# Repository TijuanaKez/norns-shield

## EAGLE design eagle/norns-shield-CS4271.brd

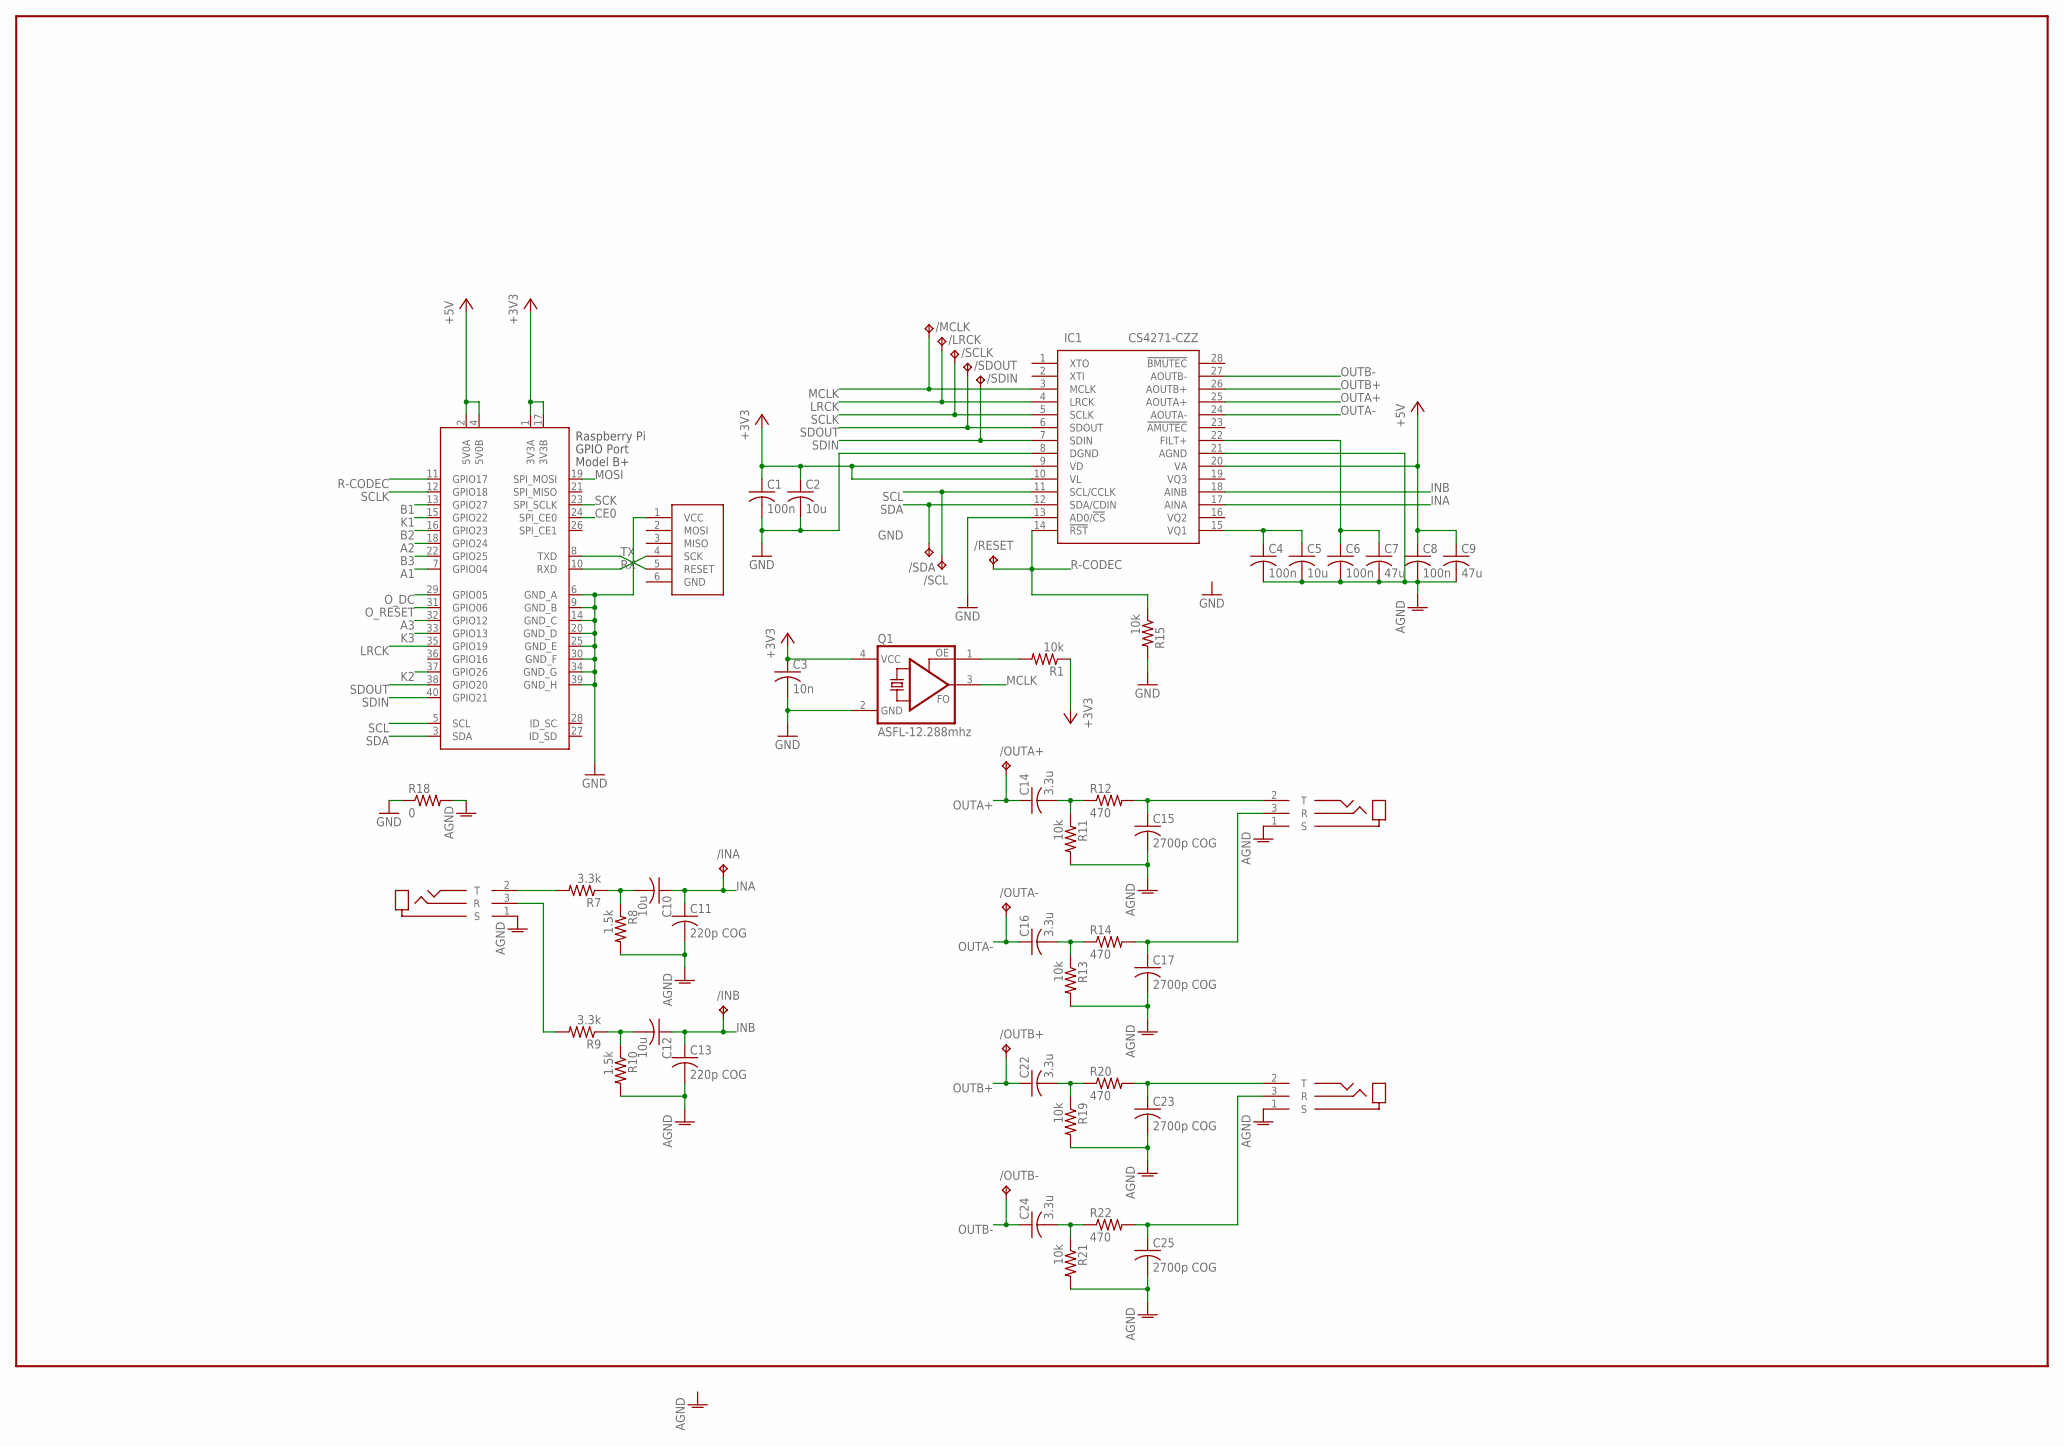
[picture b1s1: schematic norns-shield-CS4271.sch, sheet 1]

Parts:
/INA: TPTP12R; TP12R
/INB: TPTP12R; TP12R
/LRCK: TPTP12R; TP12R
/MCLK: TPTP12R; TP12R
/OUTA+: TPTP12R; TP12R
/OUTA-: TPTP12R; TP12R
/OUTB+: TPTP12R; TP12R
/OUTB-: TPTP12R; TP12R
/RESET: TPTP12R; TP12R
/SCL: TPTP12R; TP12R
/SCLK: TPTP12R; TP12R
/SDA: TPTP12R; TP12R
/SDIN: TPTP12R; TP12R
/SDOUT: TPTP12R; TP12R
C1, C4, C6, C8: 100n; C0603
C2, C5, C10, C12: 10u; C0805
C3: 10n; C0603
C7, C9: 47u; C1206
C11, C13: 220p COG; C0603
C14, C16, C22, C24: 3.3u; C0805
C15, C17, C23, C25: 2700p COG; C0603
IC1: CS4271-CZZ; SOP65P640X120-28N
J1: TRS-IN; SJ-3523-SMT
J2, J5: TRS-OUT; SJ-3523-SMT
J3: ISP-ROW
Q1: ASFL-12.288mhz; ASF
R1, R11, R13, R15, R19, R21: 10k; R0603
R7, R9: 3.3k; R0603
R8, R10: 1.5k; R0603
R12, R14, R20, R22: 470; R0603
R18: 0; R0603
X1: RASPI_BOARD_B+#_E3; RASPI_BOARD_B+_EDGES_3DRILL

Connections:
+3V3: C1.1, C2.1, C3.1, IC1.9 (VD), IC1.10 (VL), Q1.4 (VCC), R1.1, X1.1 (3V3A), X1.17 (3V3B); also elsewhere on the board
+5V: C8.1, C9.1, IC1.20 (VA), X1.2 (5V0A), X1.4 (5V0B)
A1: X1.7 (GPIO04); also elsewhere on the board
A2: X1.18 (GPIO24); also elsewhere on the board
A3: X1.32 (GPIO12); also elsewhere on the board
AGND: C4.2, C5.2, C6.2, C7.2, C8.2, C9.2, C11.2, C13.2, C15.2, C17.2, C23.2, C25.2, IC1.21 (AGND), J1.1 (S), J2.1 (S), J5.1 (S), R8.2, R10.2, R11.2, R13.2, R18.2, R19.2, R21.2
B1: X1.13 (GPIO27); also elsewhere on the board
B2: X1.16 (GPIO23); also elsewhere on the board
B3: X1.22 (GPIO25); also elsewhere on the board
CE0: X1.24 (SPI_CE0); also elsewhere on the board
FILT+: C6.1, C7.1, IC1.22 (FILT+)
GND: C1.2, C2.2, C3.2, IC1.8 (DGND), IC1.13 (AD0/!CS), J3.1 (VCC), Q1.2 (GND), R15.2, R18.1, X1.6 (GND_A), X1.9 (GND_B), X1.14 (GND_C), X1.20 (GND_D), X1.25 (GND_E), X1.30 (GND_F), X1.34 (GND_G), X1.39 (GND_H); also elsewhere on the board
INA: /INA.TP, C10.1, C11.1, IC1.17 (AINA)
INB: /INB.TP, C12.1, C13.1, IC1.18 (AINB)
K1: X1.15 (GPIO22); also elsewhere on the board
K2: X1.37 (GPIO26); also elsewhere on the board
K3: X1.33 (GPIO13); also elsewhere on the board
LRCK: /LRCK.TP, IC1.4 (LRCK), X1.35 (GPIO19)
MCLK: /MCLK.TP, IC1.3 (MCLK), Q1.3 (FO)
MOSI: X1.19 (SPI_MOSI); also elsewhere on the board
unnamed: Q1.1 (OE), R1.2
unnamed: C10.2, R7.1, R8.1
unnamed: C12.2, R9.1, R10.1
unnamed: J1.2 (T), R7.2
unnamed: J1.3 (R), R9.2
unnamed: C16.2, R13.1, R14.1
unnamed: C14.2, R11.1, R12.1
unnamed: C22.2, R19.1, R20.1
unnamed: C24.2, R21.1, R22.1
OUTA+: /OUTA+.TP, C14.1, IC1.25 (AOUTA+)
OUTA+2: C15.1, J2.2 (T), R12.2
OUTA-: /OUTA-.TP, C16.1, IC1.24 (AOUTA-)
OUTA-2: C17.1, J2.3 (R), R14.2
OUTB+: /OUTB+.TP, C22.1, IC1.26 (AOUTB+)
OUTB+2: C23.1, J5.2 (T), R20.2
OUTB-: /OUTB-.TP, C24.1, IC1.27 (AOUTB-)
OUTB-2: C25.1, J5.3 (R), R22.2
O_DC: X1.29 (GPIO05); also elsewhere on the board
O_RESET: X1.31 (GPIO06); also elsewhere on the board
R-CODEC: /RESET.TP, IC1.14 (!RST), R15.1, X1.11 (GPIO17)
RX: J3.4 (SCK), X1.10 (RXD)
SCK: X1.23 (SPI_SCLK); also elsewhere on the board
SCL: /SCL.TP, IC1.11 (SCL/CCLK), X1.5 (SCL)
SCLK: /SCLK.TP, IC1.5 (SCLK), X1.12 (GPIO18)
SDA: /SDA.TP, IC1.12 (SDA/CDIN), X1.3 (SDA)
SDIN: /SDIN.TP, IC1.7 (SDIN), X1.40 (GPIO21)
SDOUT: /SDOUT.TP, IC1.6 (SDOUT), X1.38 (GPIO20)
TX: J3.5 (RESET), X1.8 (TXD)
VQ1: C4.1, C5.1, IC1.15 (VQ1)

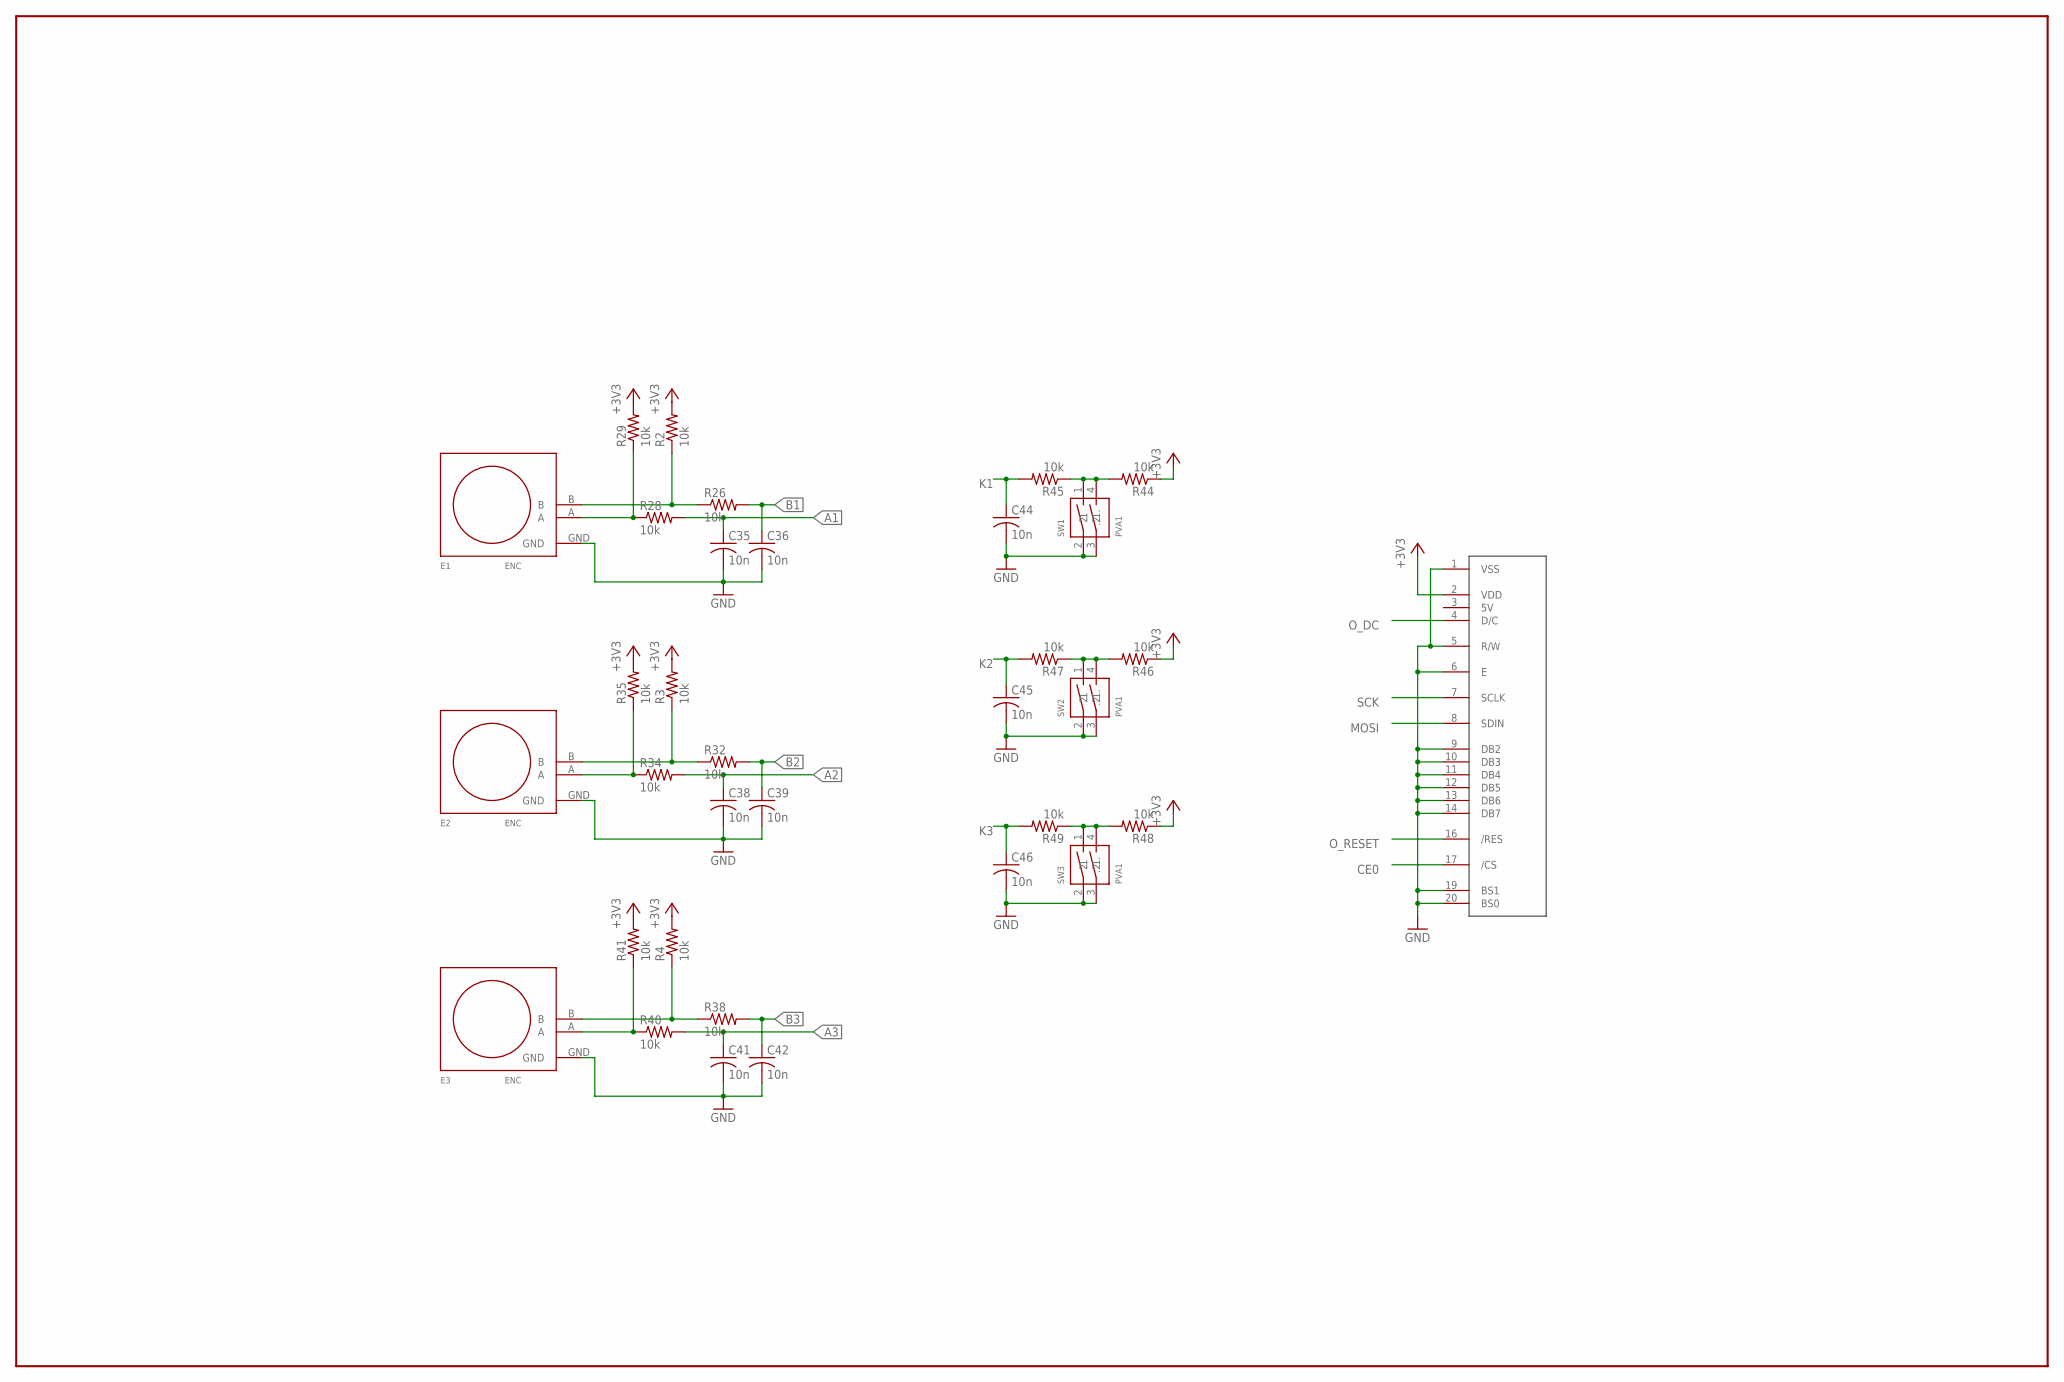
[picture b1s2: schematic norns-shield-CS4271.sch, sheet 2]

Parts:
C35, C36, C38, C39, C41, C42, C44, C45, C46: 10n; C0603
E1, E2, E3: ENC; PEC11RN
R2, R3, R4, R26, R28, R29, R32, R34, R35, R38, R40, R41, R44, R45, R46, R47, R48, R49: 10k; R0603
SW1, SW2, SW3: PVA1
U$1: OLED128X64; OLED-ALEPH

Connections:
+3V3: R2.2, R3.2, R4.2, R29.2, R35.2, R41.2, R44.1, R46.1, R48.1, U$1.2 (VDD); also elsewhere on the board
A1: C35.1, R28.2; also elsewhere on the board
A2: C38.1, R34.2; also elsewhere on the board
A3: C41.1, R40.2; also elsewhere on the board
B1: C36.1, R26.2; also elsewhere on the board
B2: C39.1, R32.2; also elsewhere on the board
B3: C42.1, R38.2; also elsewhere on the board
CE0: U$1.17 (/CS); also elsewhere on the board
GND: C35.2, C36.2, C38.2, C39.2, C41.2, C42.2, C44.2, C45.2, C46.2, E1.GND, E2.GND, E3.GND, SW1.2 (1), SW1.3 (1.), SW2.2 (1), SW2.3 (1.), SW3.2 (1), SW3.3 (1.), U$1.1 (VSS), U$1.5 (R/W), U$1.6 (E), U$1.9 (DB2), U$1.10 (DB3), U$1.11 (DB4), U$1.12 (DB5), U$1.13 (DB6), U$1.14 (DB7), U$1.19 (BS1), U$1.20 (BS0); also elsewhere on the board
K1: C44.1, R45.2; also elsewhere on the board
K2: C45.1, R47.2; also elsewhere on the board
K3: C46.1, R49.2; also elsewhere on the board
MOSI: U$1.8 (SDIN); also elsewhere on the board
unnamed: R44.2, R45.1, SW1.1 (2), SW1.4 (.2)
unnamed: R46.2, R47.1, SW2.1 (2), SW2.4 (.2)
unnamed: R48.2, R49.1, SW3.1 (2), SW3.4 (.2)
unnamed: E1.A, R28.1, R29.1
unnamed: E1.B, R2.1, R26.1
unnamed: E2.B, R3.1, R32.1
unnamed: E2.A, R34.1, R35.1
unnamed: E3.B, R4.1, R38.1
unnamed: E3.A, R40.1, R41.1
O_DC: U$1.4 (D/C); also elsewhere on the board
O_RESET: U$1.16 (/RES); also elsewhere on the board
SCK: U$1.7 (SCLK); also elsewhere on the board

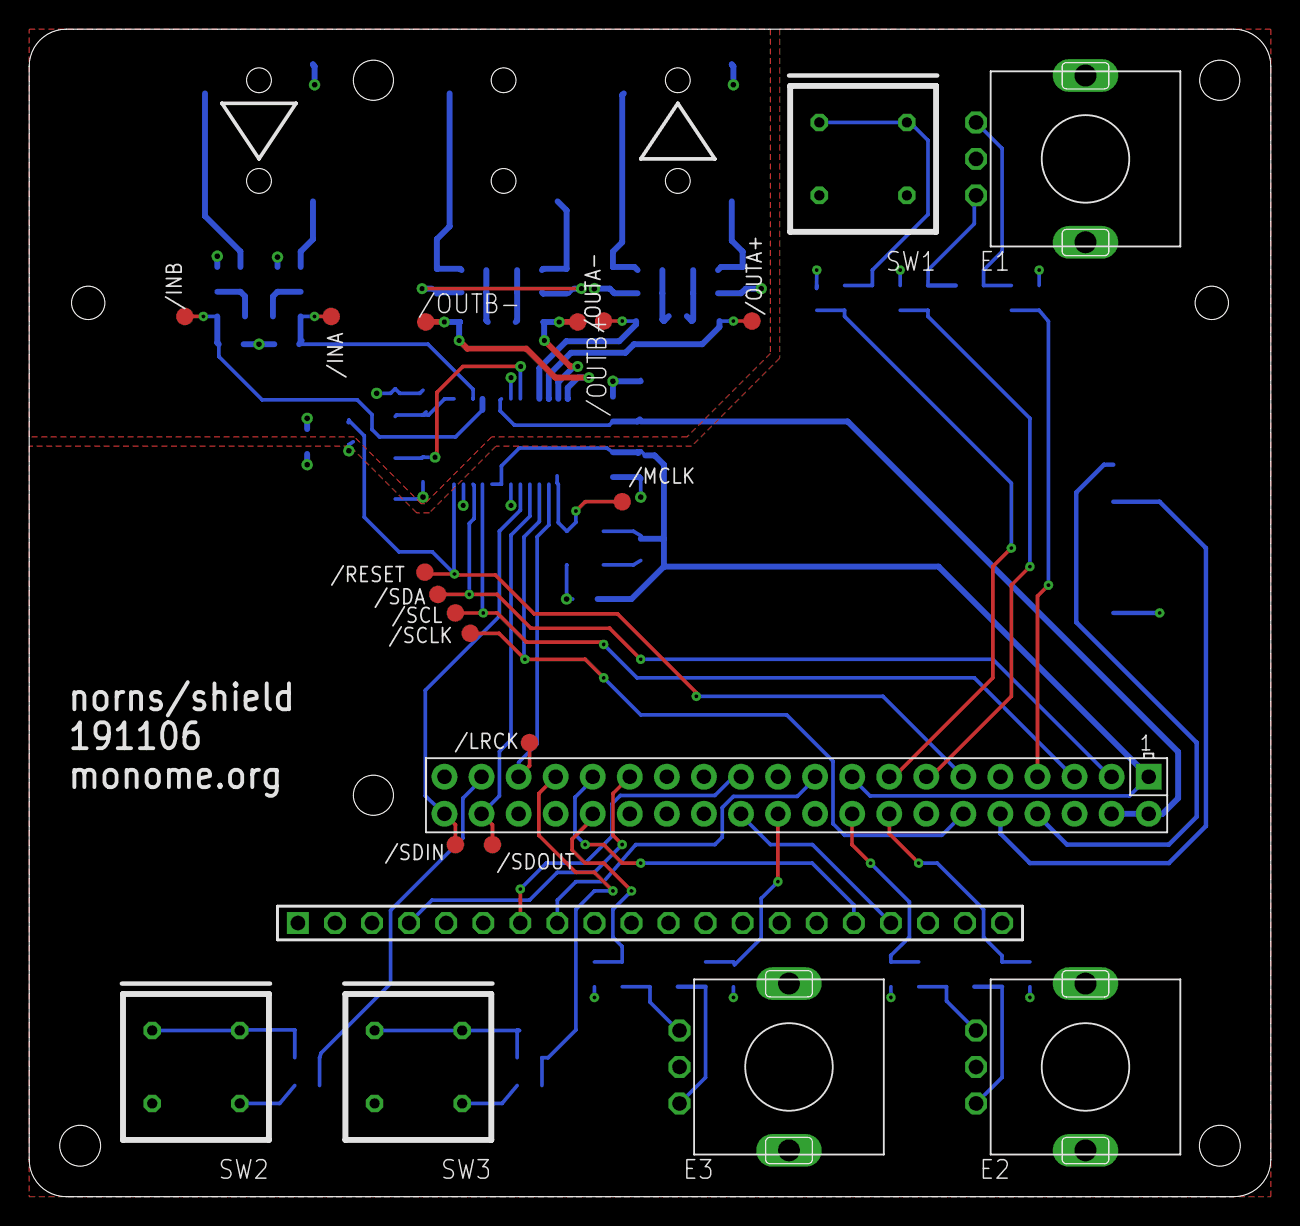
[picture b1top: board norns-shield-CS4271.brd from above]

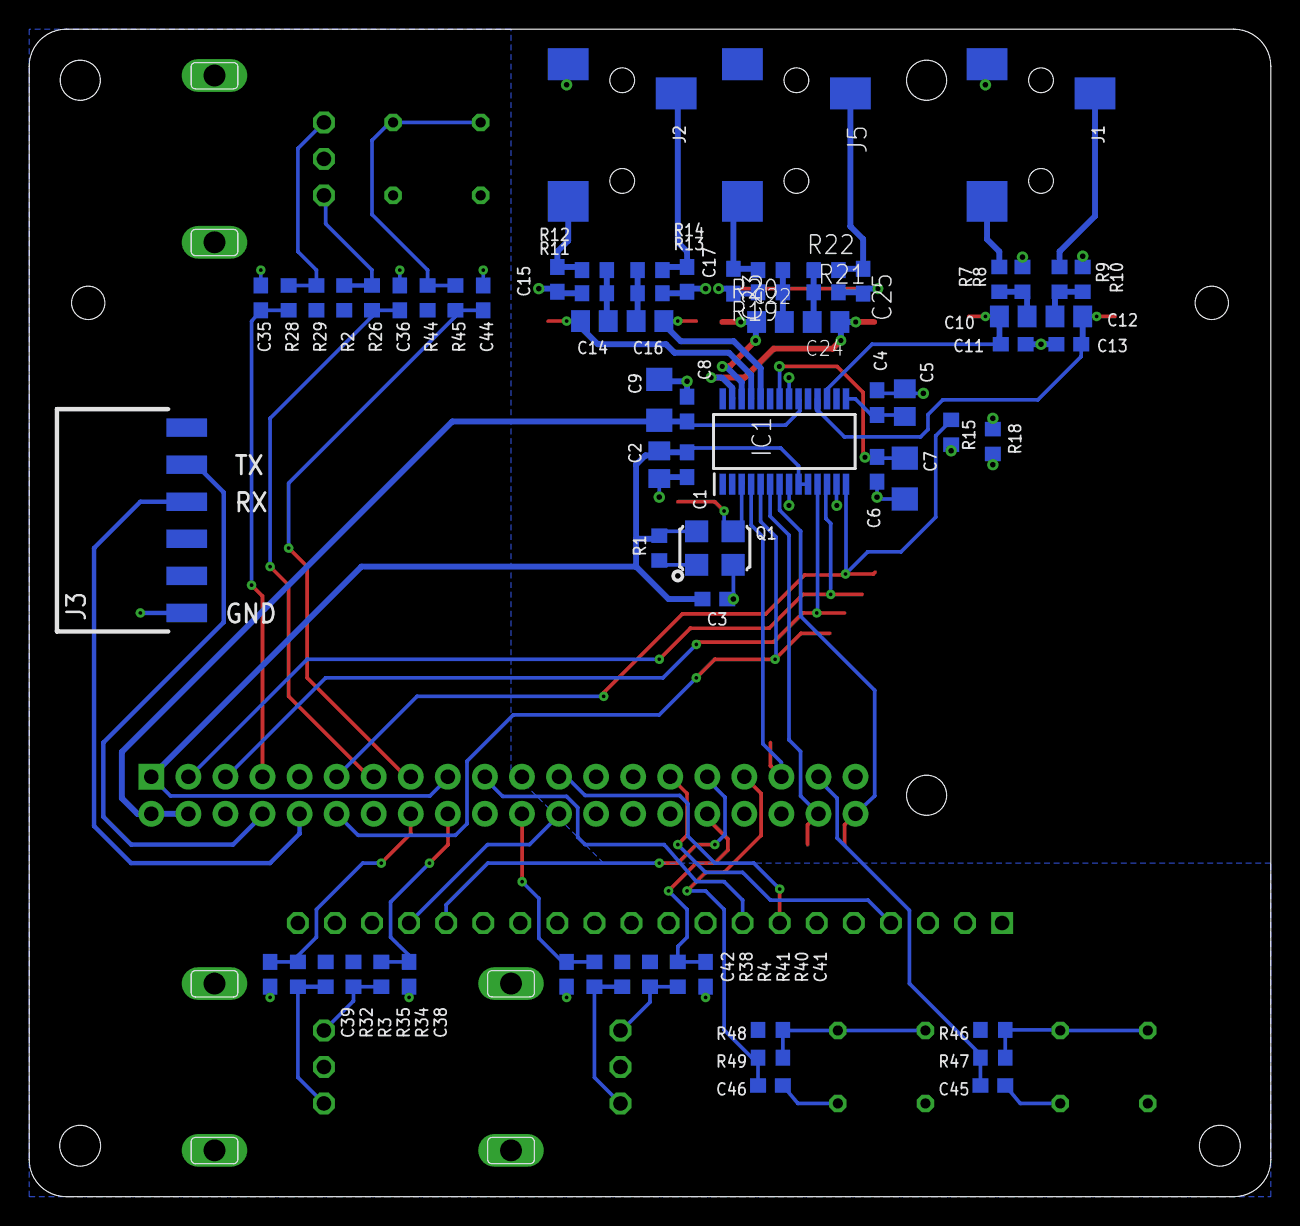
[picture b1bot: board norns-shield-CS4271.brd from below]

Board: 2 copper layers, 85.1 x 80.0 mm, 91 parts (69 on the bottom side), 58 nets.

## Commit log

2021-10-30 Initial CS4271 Mod
